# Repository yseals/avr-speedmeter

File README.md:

# avr-speedmeter
プログラマー5年目(2009年頃)のときの製作物です

## 概要
ATTiny2313を使ったデジタルスピードメーターで<br>
ヘッドアップディスプレイ(HUD)として使用も可能です。<br>
車速パルスを拾い、7セグLEDでスピード表示します。

## 動作環境
2009年当時の環境で開発
- ATTiny2313 10MHzで動作
- AVR Studio4
- WinAVR

## 背景
乗っていた車にHUDつけたいなと思ったのがきっかけで作りました。<br>
回路基板製作もやってみたかったので、Eagle（CAD）使って、<br>
回路図作り、最終的にはガーバーデータまで作成し、基板屋さんへ基板製作依頼しました。

## 使用方法
1. AVRマイコンにヒューズ設定.txtの内容を書き込んでください

1. main.hの設定を調整します
   | 設定項目 | 設定内容 |
   | --- | --- |
   | MISEC | define定義無しの場合、100us単位で調整可能、<br> define定義ありの場合1ms単位で設定可能 |
   | DISPLAY_CHG_TIME_HUD | HUDモードかつヘッドライトOFF時の7セグ1桁への出力時間 |
   | DISPLAY_OFF_TIME_HUD | HUDモードかつヘッドライトOFF時の7セグ1桁への出力OFF時間<br> 出力時間のうちOFFする時間設定し減光させる |
   | DISPLAY_CHG_TIME_ILUM_HUD | HUDモードかつヘッドライトON時の7セグ1桁への出力時間 |
   | DISPLAY_OFF_TIME_ILUM_HUD | HUDモードかつヘッドライトON時の7セグ1桁への出力OFF時間<br> 出力時間のうちOFFする時間設定し減光させる |
   | COUNTER_TIME | 車速パルスの測定周期かつ、スピード表示の更新周期<br>MES_COUNT x COUNTER_TIMEで1.4秒の値になるように設定する<br>1km/hが車速パルスで0.7Hzほどの周期のため |
   | ILUMI_TIME | イルミネーションON/OFFチェック周期 |
   | HUD_TIME | 起動時のHUDジャンパー確認までの待機時間 |
   | INITIAL_ON_TIME | 起動時の7セグ点灯チェックの点灯時間 |
   | INITIAL_OFF_TIME | 起動時の7セグ点灯チェック終了後の待機時間 |
   | MES_COUNT | 車速パルス測定回数、COUNTER_TIMEと合わせて設定<br>COUNTER_TIMEを伸ばすと、表示更新が遅くなるので、<br>MES_COUNTと組み合わせて更新間隔と測定時間を調整用 |
   | DISP_DIGIT | 固定値 3桁であることを設定（変更禁止） |
   | DISP_VALUE_NULL | 固定値 10とすることで7セグ非表示としてる（変更禁止） |

1. マイコンに書き込んで動作させてください

## 注意事項
- 本回路図は動作確認済みですが、製作・接続は自己責任で行ってください。

- 車など外部機器との接続により生じた破損や事故について、制作者は一切の責任を負いません。

## ライセンス
This software is released under the MIT License, see LICENSE.

## 作者
yseals

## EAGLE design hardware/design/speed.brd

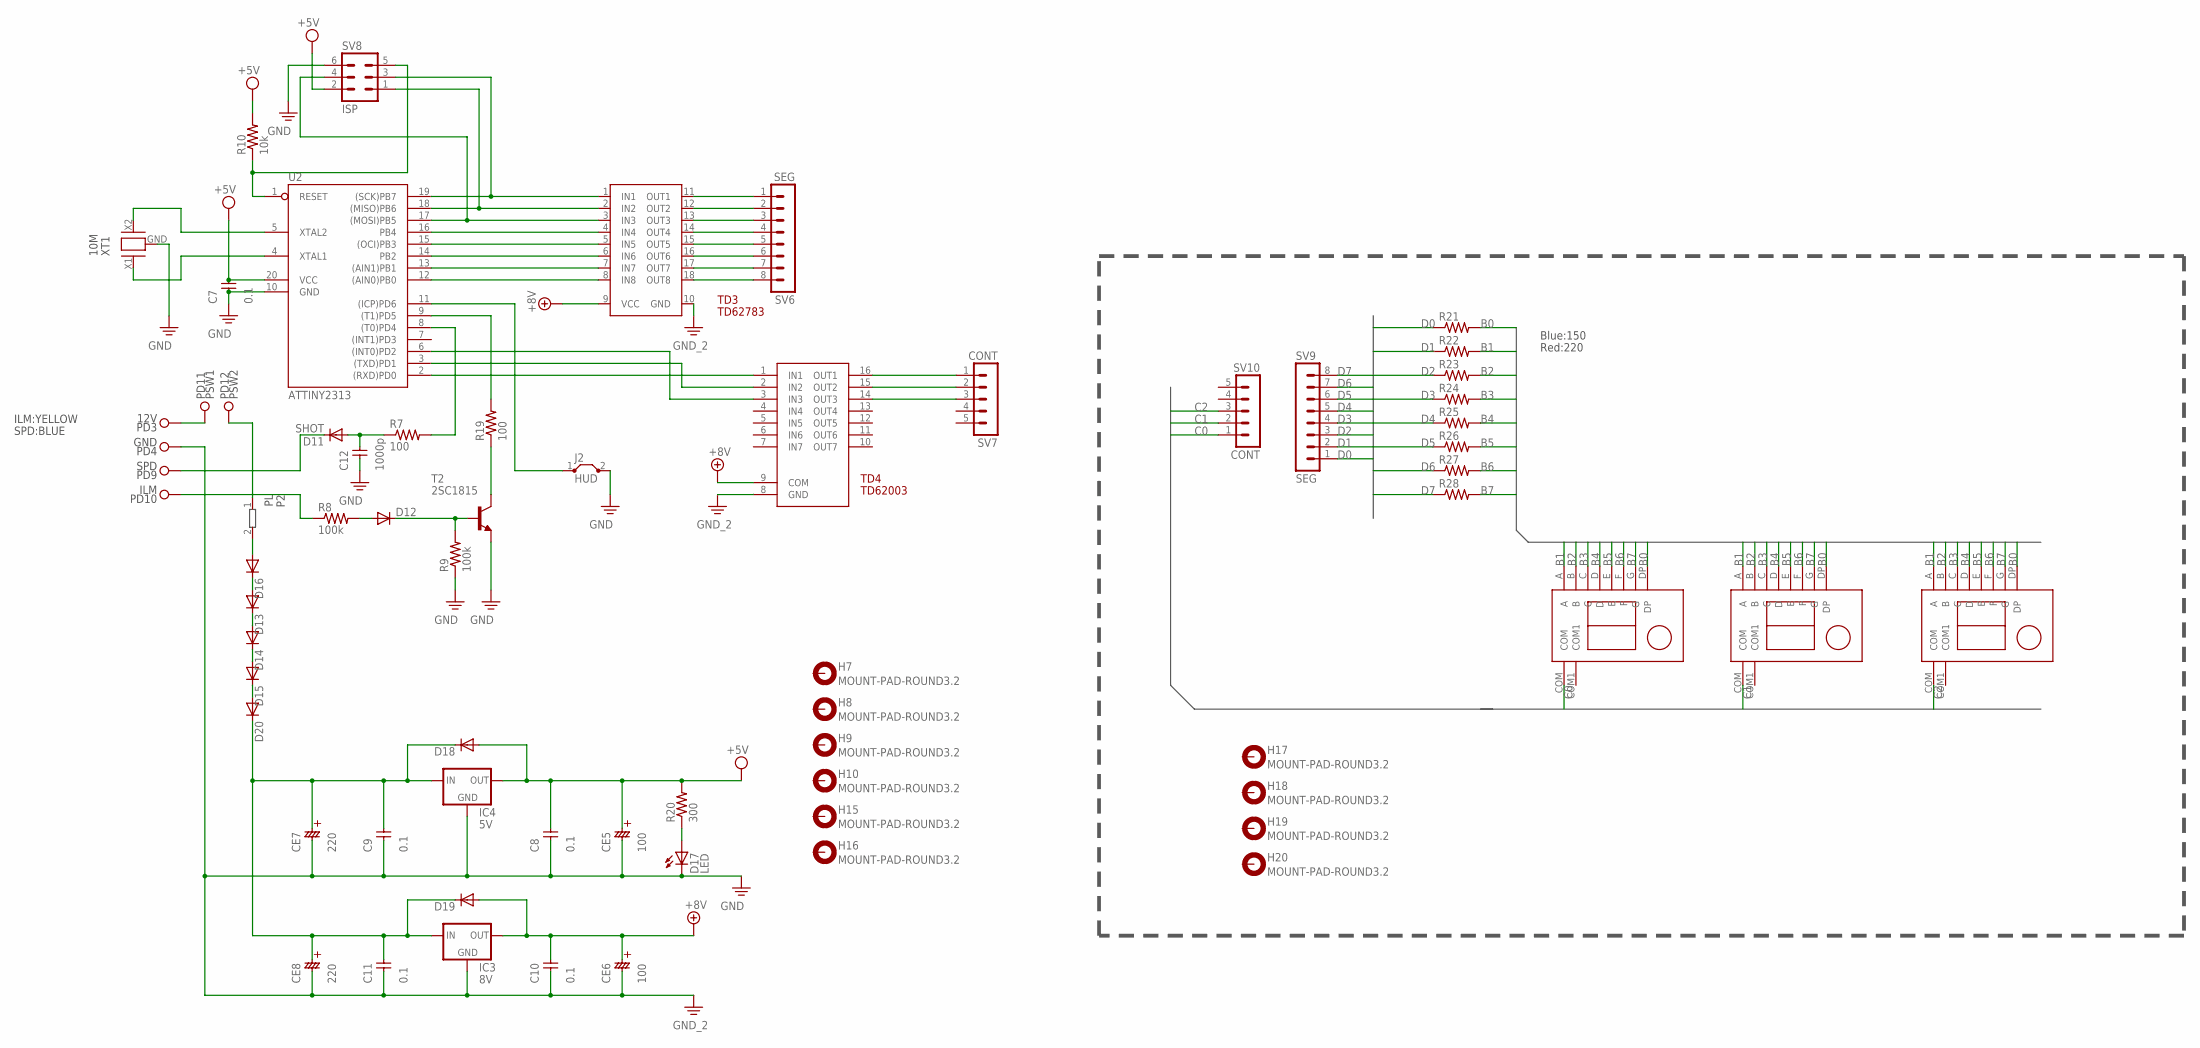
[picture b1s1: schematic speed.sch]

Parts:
C7, C8, C9, C10, C11: 0.1; C-2,5
C12: 1000p; C-2,5
CE5, CE6: 100; ELC-2,5
CE7, CE8: 220; ELC-5
D11: SHOT; 0204V
D12: 1N4004"; DIP-2-10
D13, D14, D15, D16, D18, D19, D20: 1N4004T; 0204V
D17: LED; LED5MM
H7, H8, H9, H10, H15, H16, H17, H18, H19, H20: MOUNT-PAD-ROUND3.2; 3,2-PAD
IC3: 8V; 78XXL
IC4: 5V; 78XXS
J2: HUD; JUMP2
LED4, LED5, LED6: C-551X; 7SEG-0.56
P2: PL; 0204/5
PD3: 12V; CFPAD
PD4: GND; CFPAD
PD9: SPD; CFPAD
PD10: ILM; CFPAD
PD11: PSW1; CPPAD
PD12: PSW2; CPPAD
R7, R19: 100; 0204/7
R8, R9: 100k; 0204/7
R10: 10k; 0204/7
R20: 300; 0204V
R21, R22, R23, R24, R25, R26, R27, R28: RES7; 0204/7
SV6, SV9: SEG; MA08-1
SV7, SV10: CONT; MA05-1
SV8: ISP; ML6
T2: 2SC1815; TO92
TD3: TD62783; DIP-18
TD4: TD62003; DIP-16
U2: ATTINY2313; DIP-20
XT1: 10M; CELALOCK

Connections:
+5V/1: C7.2, C8.2, CE5.PLUS, D18.1 (A), IC4.OUT, R10.2, R20.2, SV8.2, U2.20 (VCC)
+9V: C10.2, CE6.PLUS, D19.1 (A), IC3.IN (OUT), TD3.9 (VCC), TD4.9 (COM)
B0: LED4.DP, LED5.DP, LED6.DP, R21.2
B1: LED4.A, LED5.A, LED6.A, R22.2
B2: LED4.B, LED5.B, LED6.B, R23.2
B3: LED4.C, LED5.C, LED6.C, R24.2
B4: LED4.D, LED5.D, LED6.D, R25.2
B5: LED4.E, LED5.E, LED6.E, R26.2
B6: LED4.F, LED5.F, LED6.F, R27.2
B7: LED4.G, LED5.G, LED6.G, R28.2
C0: LED4.COM, SV10.1
C1: LED5.COM, SV10.2
C2: LED6.COM, SV10.3
D0: R21.1, SV9.1
D1: R22.1, SV9.2
D2: R23.1, SV9.3
D3: R24.1, SV9.4
D4: R25.1, SV9.5
D5: R26.1, SV9.6
D6: R27.1, SV9.7
D7: R28.1, SV9.8
unnamed: R10.1, SV8.5, U2.1 (RESET)
unnamed: SV8.3, TD3.1 (IN1), U2.19 ((SCK)PB7)
unnamed: SV8.1, TD3.2 (IN2), U2.18 ((MISO)PB6)
unnamed: SV8.4, TD3.3 (IN3), U2.17 ((MOSI)PB5)
unnamed: TD3.4 (IN4), U2.16 (PB4)
unnamed: TD3.5 (IN5), U2.15 ((OCI)PB3)
unnamed: TD3.6 (IN6), U2.14 (PB2)
unnamed: TD3.7 (IN7), U2.13 ((AIN1)PB1)
unnamed: R7.2, U2.8 ((T0)PD4)
unnamed: J2.1, U2.11 ((ICP)PD6)
unnamed: C12.2, D11.1 (A), R7.1
unnamed: D11.2 (C), PD9.CPAD
unnamed: D12.A, R8.2
unnamed: PD10.CPAD, R8.1
unnamed: U2.5 (XTAL2), XT1.X2
unnamed: U2.4 (XTAL1), XT1.X1
unnamed: R19.2, U2.9 ((T1)PD5)
unnamed: TD3.8 (IN8), U2.12 ((AIN0)PB0)
unnamed: TD4.1 (IN1), U2.2 ((RXD)PD0)
unnamed: TD4.2 (IN2), U2.3 ((TXD)PD1)
unnamed: TD4.3 (IN3), U2.6 ((INT0)PD2)
unnamed: SV7.1, TD4.16 (OUT1)
unnamed: SV7.2, TD4.15 (OUT2)
unnamed: SV7.3, TD4.14 (OUT3)
unnamed: C9.2, C11.2, CE7.PLUS, CE8.PLUS, D18.2 (C), D19.2 (C), D20.2 (C), IC3.OUT (IN), IC4.IN
unnamed: D12.C, R9.2, T2.1 (B)
unnamed: P2.1, PD12.CPPAD
unnamed: PD3.CPAD, PD11.CPPAD
unnamed: SV6.1, TD3.11 (OUT1)
unnamed: SV6.2, TD3.12 (OUT2)
unnamed: SV6.3, TD3.13 (OUT3)
unnamed: SV6.4, TD3.14 (OUT4)
unnamed: SV6.5, TD3.15 (OUT5)
unnamed: SV6.6, TD3.16 (OUT6)
unnamed: SV6.7, TD3.17 (OUT7)
unnamed: SV6.8, TD3.18 (OUT8)
unnamed: D16.1 (A), P2.2
unnamed: D13.1 (A), D16.2 (C)
unnamed: D13.2 (C), D14.1 (A)
unnamed: D14.2 (C), D15.1 (A)
unnamed: R19.1, T2.2 (C)
unnamed: D17.A, R20.1
unnamed: D15.2 (C), D20.1 (A)
PE: C7.1, C8.1, C9.1, C10.1, C11.1, C12.1, CE5.MAINAS, CE6.MAINAS, CE7.MAINAS, CE8.MAINAS, D17.K (C), IC3.GND, IC4.GND, J2.2, PD4.CPAD, R9.1, SV8.6, T2.3 (E), TD3.10 (GND), TD4.8 (GND), U2.10 (GND), XT1.GND

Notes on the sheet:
Blue:150
Red:220
ILM:YELLOW
SPD:BLUE

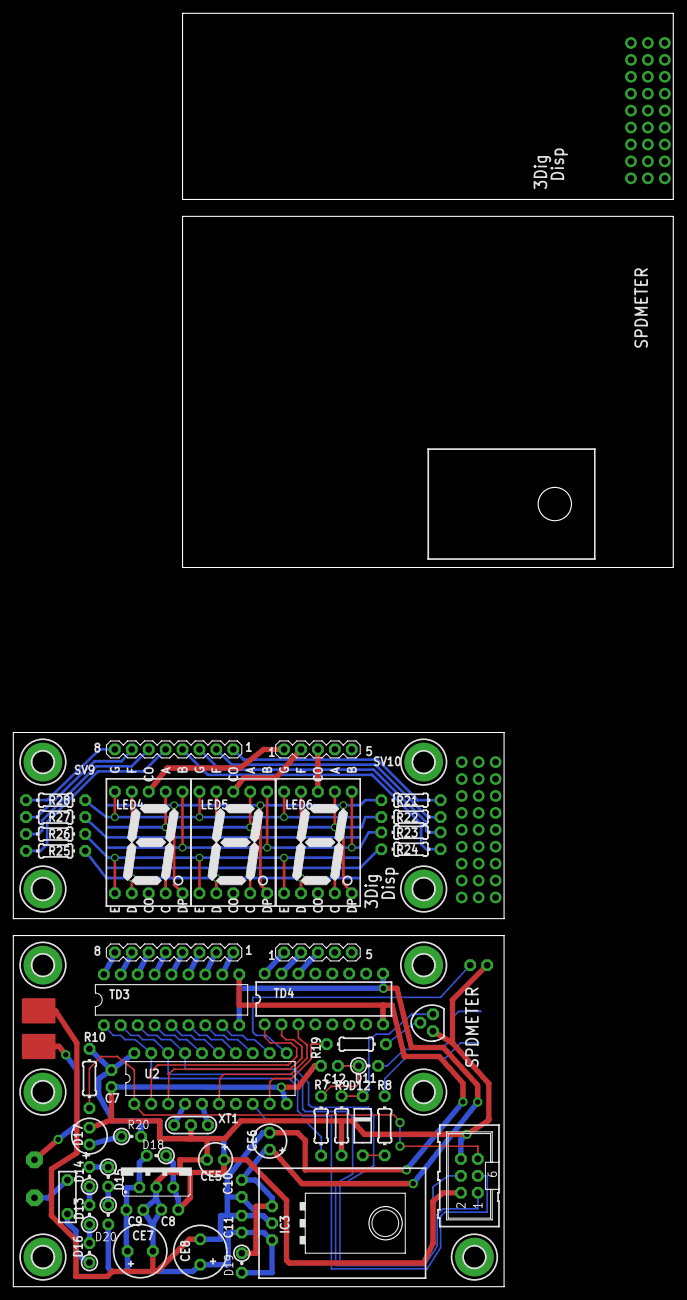
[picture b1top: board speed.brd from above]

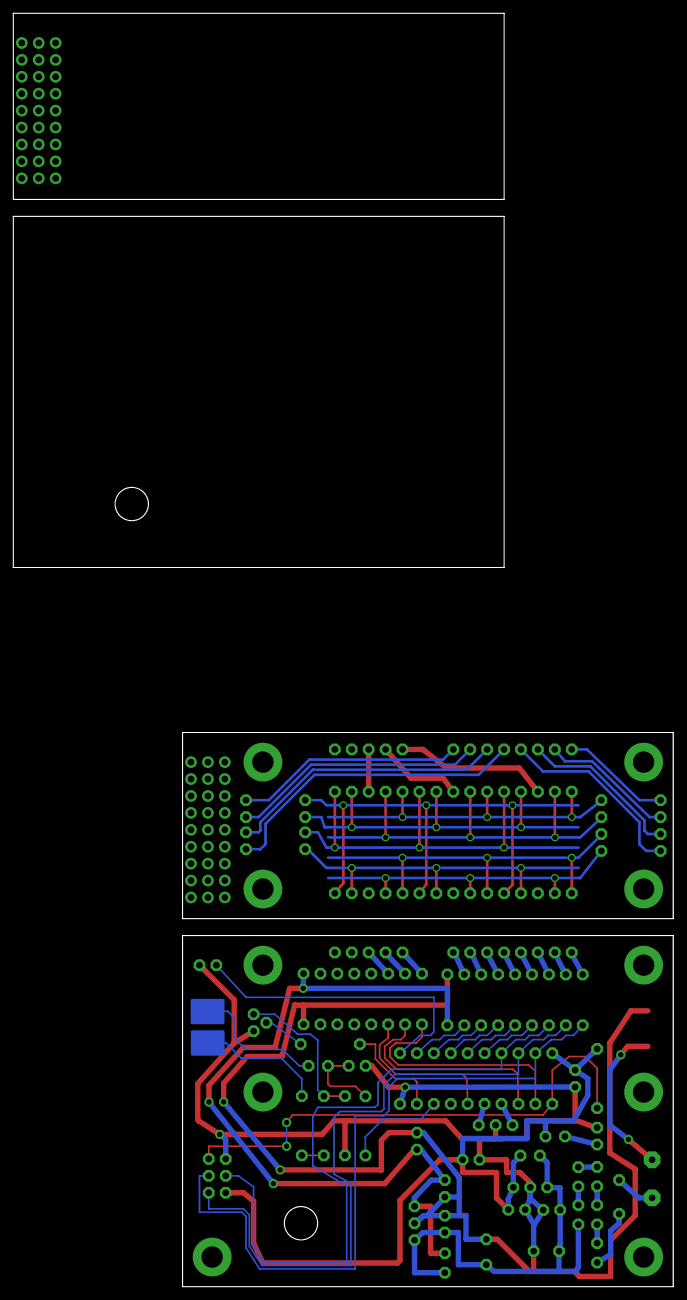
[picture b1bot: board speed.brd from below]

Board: 2 copper layers, 99.1 x 191.1 mm, 69 parts (2 on the bottom side), 65 nets.

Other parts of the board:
U$1, U$2: TO-220HEATSINKN

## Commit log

2026-04-30 README新規登録
    Added detailed setup and usage instructions for the digital speedometer project.
2026-04-30 README更新
    Updated README with additional setup and usage instructions.
2026-05-01 Create .gitattribute
    改行コードを変更しない設定
2026-05-01 初期バージョン
    初期バージョン登録
2026-05-01 Update README with images and usage instructions
    Added images and expanded usage instructions in README.
